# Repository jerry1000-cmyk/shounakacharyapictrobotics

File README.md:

# Robotics Tasks

# Coding (Primary Domain)

## 1)Linux commands
In the Linux Folder you will find a pdf with screenshots of all the linux commands and their executions .
I learned the basic linux commands from video series provided and executed some of them

## 2) Github
In the Github folder you will find the pdf with git commands and their explanations and handwritten notes .
I watched multiple git tutorials to write my notes

## 3)Arduino 
In the Arduino folder you will find the code for a blinking LED and also a video of its execution on a simulator

## 4)OpenCV (Research Task)
In the OpenCV folder you will find multiple .py files containing scripts of things i learned as i researched about opencv
also it contains a face detection and face recognizer code

# Electronics (Secondary Domain)

## Kicad
In the Kicad Folder you will find the completed Schematic and PCB design 
Parts used :
- ESP32 - Microcontroller for controlling speed and direction
- L293D - Motor Driver to take input from ESP and turn the motors
- L7805 - Convert Any voltage(upto 12V) into 5V to keep electrical components safe
- AMS51117-3.3 - Convert 5V to 3.3V for the ESP
- Screw Terminals - 3 Screw Terminals 2 for motors and 1 for battery to screw the wires of the components in

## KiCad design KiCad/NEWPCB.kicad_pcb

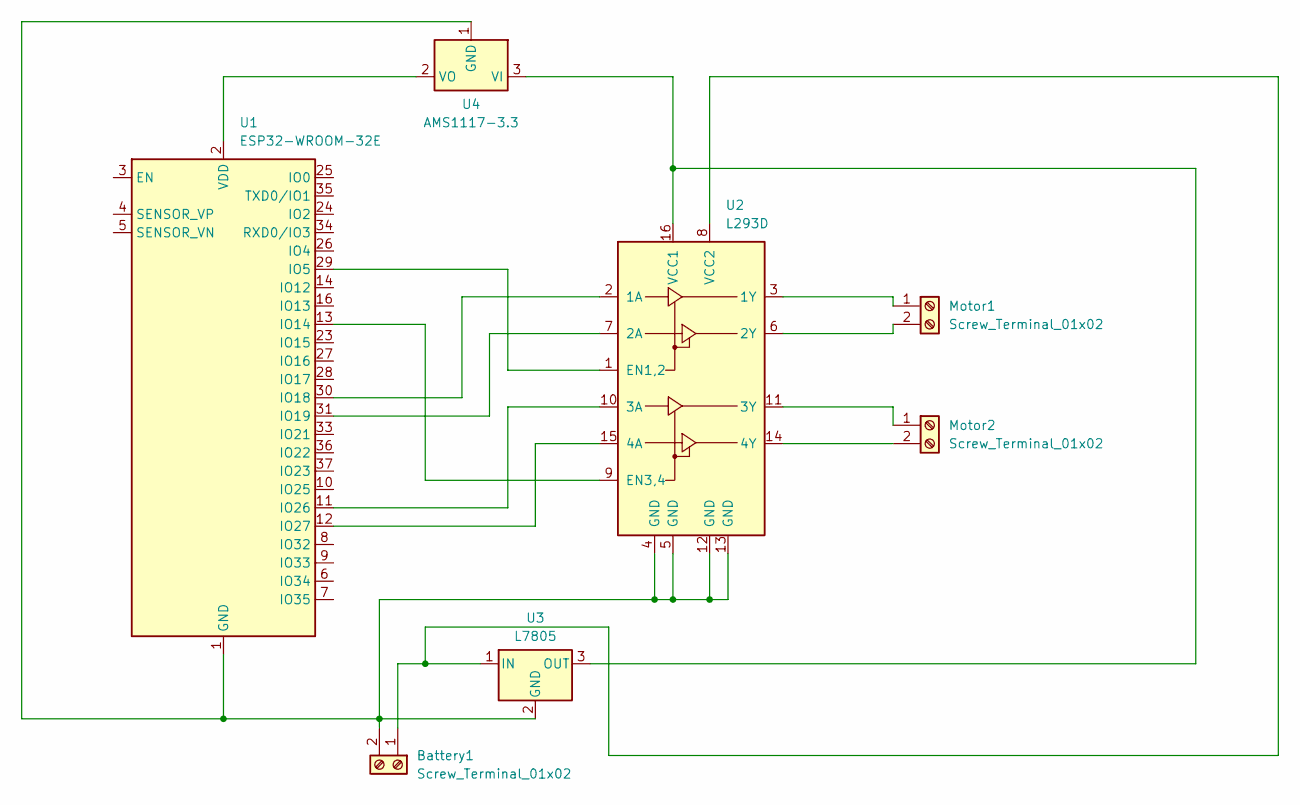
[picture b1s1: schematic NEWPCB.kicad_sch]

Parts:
Battery1: Screw_Terminal_01x02; TerminalBlock_CUI_TB007-508-02_1x02_P5.08mm_Horizontal
Motor1, Motor2: Screw_Terminal_01x02; TerminalBlock_CUI_TB007-508-02_1x02_P5.08mm_Horizontal
U1: ESP32-WROOM-32E; ESP32-WROOM-32D
U2: L293D; DIP-16_W7.62mm
U3: L7805; TO-220-3_Vertical
U4: AMS1117-3.3; SOT-223-3_TabPin2

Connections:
unnamed: Battery1.1, U2.8 (VCC2), U3.1 (IN)
unnamed: Battery1.2, U1.1 (GND), U1.15 (GND), U1.38 (GND), U1.39 (GND), U2.4 (GND), U2.5 (GND), U2.12 (GND), U2.13 (GND), U3.2 (GND), U4.1 (GND)
unnamed: Motor1.1, U2.3 (1Y)
unnamed: Motor1.2, U2.6 (2Y)
unnamed: Motor2.1, U2.11 (3Y)
unnamed: Motor2.2, U2.14 (4Y)
unnamed: U1.29 (IO5), U2.1 (EN1,2)
unnamed: U1.13 (IO14), U2.9 (EN3,4)
unnamed: U1.30 (IO18), U2.2 (1A)
unnamed: U1.31 (IO19), U2.7 (2A)
unnamed: U1.11 (IO26), U2.10 (3A)
unnamed: U1.12 (IO27), U2.15 (4A)
unnamed: U1.2 (VDD), U4.2 (VO)
unnamed: U2.16 (VCC1), U3.3 (OUT), U4.3 (VI)

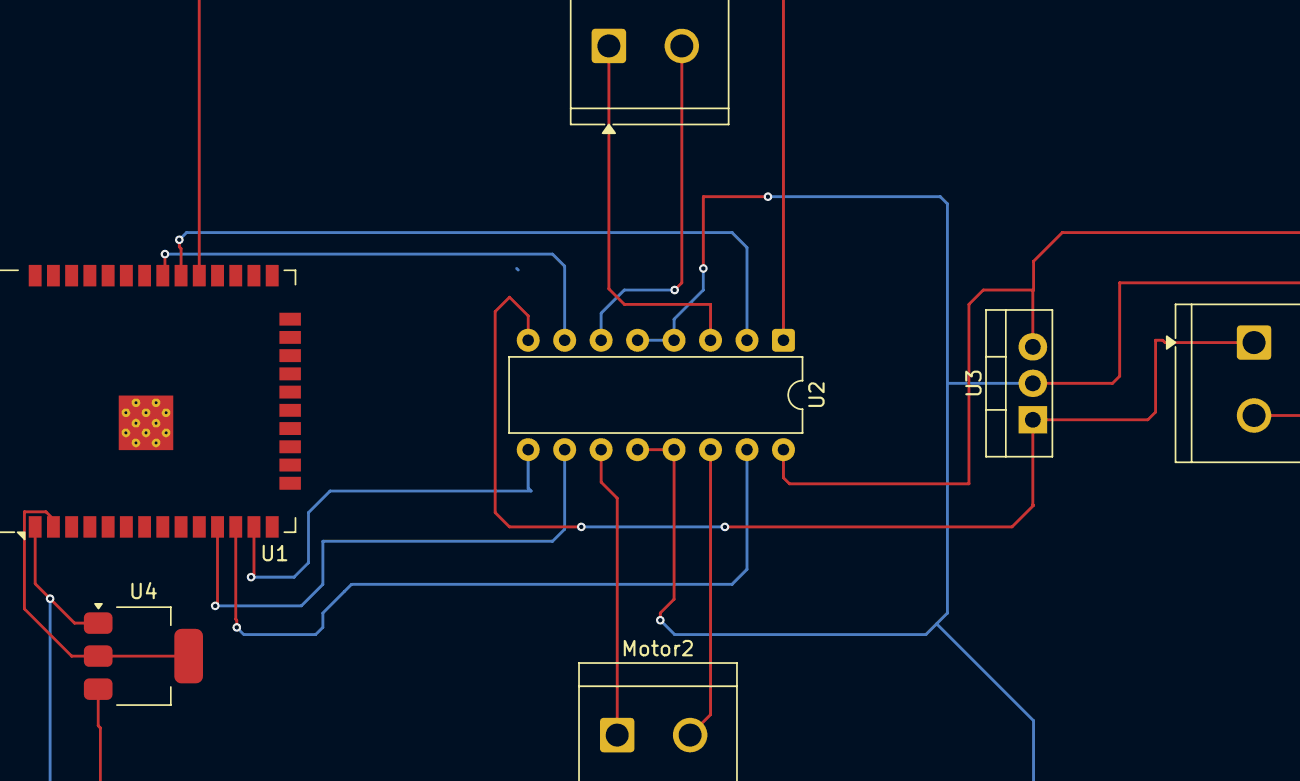
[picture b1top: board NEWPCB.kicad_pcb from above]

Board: 2 copper layers, 7 parts (0 on the bottom side), 14 nets.

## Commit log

2026-01-27 Arduino done
2026-01-29 Completed OPENCV
2026-02-01 Linux Done
2026-02-01 Edited Readme
2026-02-01 GITHUB DONE
2026-02-02 KICAD DONE
2026-02-05 Github Updated
2026-02-06 Added New Tinkercad Video to Arduino
